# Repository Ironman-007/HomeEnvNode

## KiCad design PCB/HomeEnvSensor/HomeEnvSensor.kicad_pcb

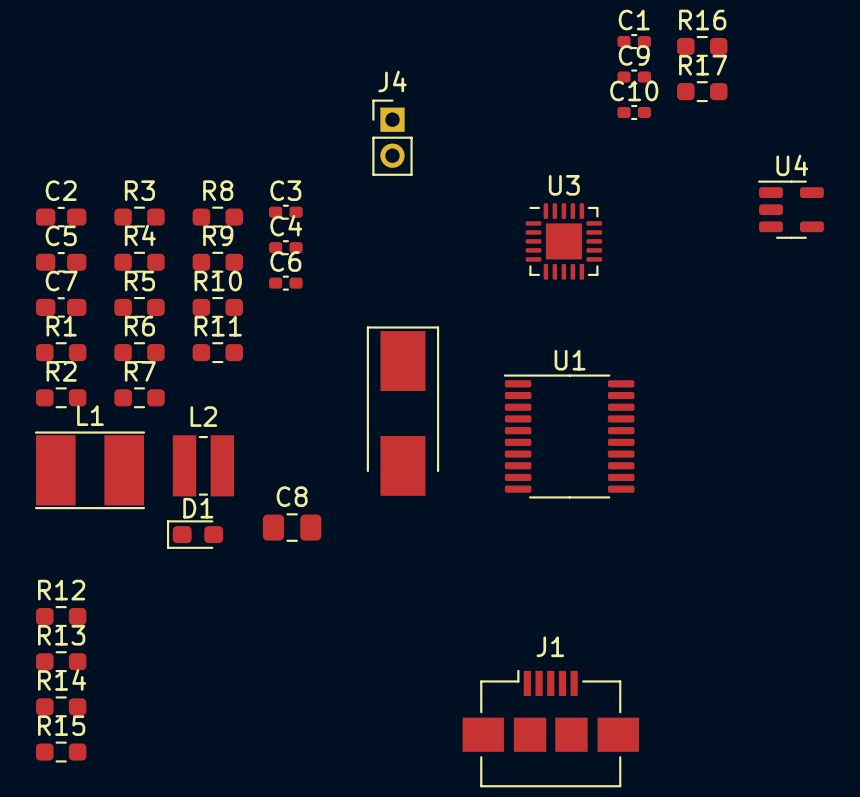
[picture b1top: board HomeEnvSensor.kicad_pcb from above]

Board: 2 copper layers, 36 parts (0 on the bottom side), 25 nets, no tracks yet.

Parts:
C1, C4, C6: 0.1uF; C_0402_1005Metric_Pad0.74x0.62mm_HandSolder
C2: 10uF; C_0603_1608Metric_Pad1.08x0.95mm_HandSolder
C3: 0.01uF; C_0402_1005Metric_Pad0.74x0.62mm_HandSolder
C5, C7: 4.7uF; C_0603_1608Metric_Pad1.08x0.95mm_HandSolder
C8: 22uF; C_0805_2012Metric_Pad1.18x1.45mm_HandSolder
C9, C10: 22pF; C_0402_1005Metric_Pad0.74x0.62mm_HandSolder
D1: RED; LED_0603_1608Metric_Pad1.05x0.95mm_HandSolder
J1: USB_B_Micro; USB_Micro-B_Amphenol_10104110_Horizontal
J4: Battery; PinHeader_1x02_P2.00mm_Vertical
L1: 22uH; L_Taiyo-Yuden_NR-40xx_HandSoldering
L2: 4.7uH; L_Wuerth_MAPI-3015
R1: 0; R_0603_1608Metric_Pad0.98x0.95mm_HandSolder
R2, R9: 10k; R_0603_1608Metric_Pad0.98x0.95mm_HandSolder
R3: 100; R_0603_1608Metric_Pad0.98x0.95mm_HandSolder
R4: 7.32M; R_0603_1608Metric_Pad0.98x0.95mm_HandSolder
R5: 5.62M; R_0603_1608Metric_Pad0.98x0.95mm_HandSolder
R6: 330K; R_0603_1608Metric_Pad0.98x0.95mm_HandSolder
R7: 8.45M; R_0603_1608Metric_Pad0.98x0.95mm_HandSolder
R8: 4.22M; R_0603_1608Metric_Pad0.98x0.95mm_HandSolder
R10: 8.25M; R_0603_1608Metric_Pad0.98x0.95mm_HandSolder
R11: 4.75M; R_0603_1608Metric_Pad0.98x0.95mm_HandSolder
R12, R13, R14, R15: 499k; R_0603_1608Metric_Pad0.98x0.95mm_HandSolder
R16, R17: 4.7K; R_0603_1608Metric_Pad0.98x0.95mm_HandSolder
U1: STM32L031F6P7; TSSOP-20_4.4x6.5mm_P0.65mm
U3: BQ25570; QFN-20-1EP_3.5x3.5mm_P0.5mm_EP2x2mm
U4: MCP73831-2-OT; SOT-23-5
Y1: 32.768KHz; Crystal_SMD_0603-2Pin_6.0x3.5mm_HandSoldering

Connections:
+3.3V: C1.1, C8.1, L2.2, R16.1, R17.1, U1.5 (VDDA), U1.16 (VDD), U3.14 (VOUT)
+5V: C6.1, D1.2 (A), J1.1 (VBUS), R14.2, U4.4 (V_{DD})
+BATT: C7.1, J4.1, R12.2, U3.18 (VBAT), U4.3 (V_{BAT})
/Power/VSTOR: C4.1, C5.1, R1.2, U3.3 (VOC_SAMP), U3.19 (VSTOR)
ADC_IN0: R12.1, R13.2, U1.6 (PA0)
ADC_IN1: R14.1, R15.2, U1.7 (PA1)
GND: C1.2, C2.2, C3.2, C4.2, C5.2, C6.2, C7.2, C8.2, C9.2, C10.2, J1.5 (GND), J1.6 (Shield), J4.2, R2.1, R5.1, R8.1, R9.1, R11.1, R13.1, R15.1, U1.15 (VSS), U3.1 (VSS), U3.9 (VSS), U3.15 (VSS), U3.17 (VSS), U3.21 (VSS), U4.2 (V_{SS})
unnamed: D1.1 (K), R3.2
unnamed: C10.1, U1.2 (PC14), Y1.1
unnamed: C9.1, U1.3 (PC15), Y1.2
unnamed: L1.2, U3.20 (LBOOST)
unnamed: L2.1, U3.16 (LBUCK)
unnamed: R6.1, R7.2, U3.10 (OK_HYST)
unnamed: R7.1, R8.2, U3.11 (OK_PROG)
unnamed: R4.1, R5.2, U3.7 (VBAT_OV)
unnamed: R1.1, U3.6 (VOUT_EN)
unnamed: R10.1, R11.2, U3.12 (VOUT_SET)
unnamed: R4.2, R6.2, R10.2, U3.8 (VRDIV)
unnamed: C3.1, U3.4 (VREF_SAMP)
unnamed: R2.2, U3.5 (~EN)
unnamed: R9.2, U4.5 (PROG)
unnamed: R3.1, U4.1 (STAT)
SC: C2.1, L1.1, U3.2 (VIN_DC)
SCL: R16.2, U1.17 (PA9)
SDA: R17.2, U1.18 (PA10)

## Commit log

2023-06-19 udated by FZ from Windows
